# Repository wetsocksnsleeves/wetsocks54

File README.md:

# What
- 54 key ortholinear column staggered split keyboard
- Fork of cheapino, circuit utilises japanese matrix as well

# Future
- Working on v2 with better layout. Changing case and pcb
- Fixed some encoder issues in the pcb already

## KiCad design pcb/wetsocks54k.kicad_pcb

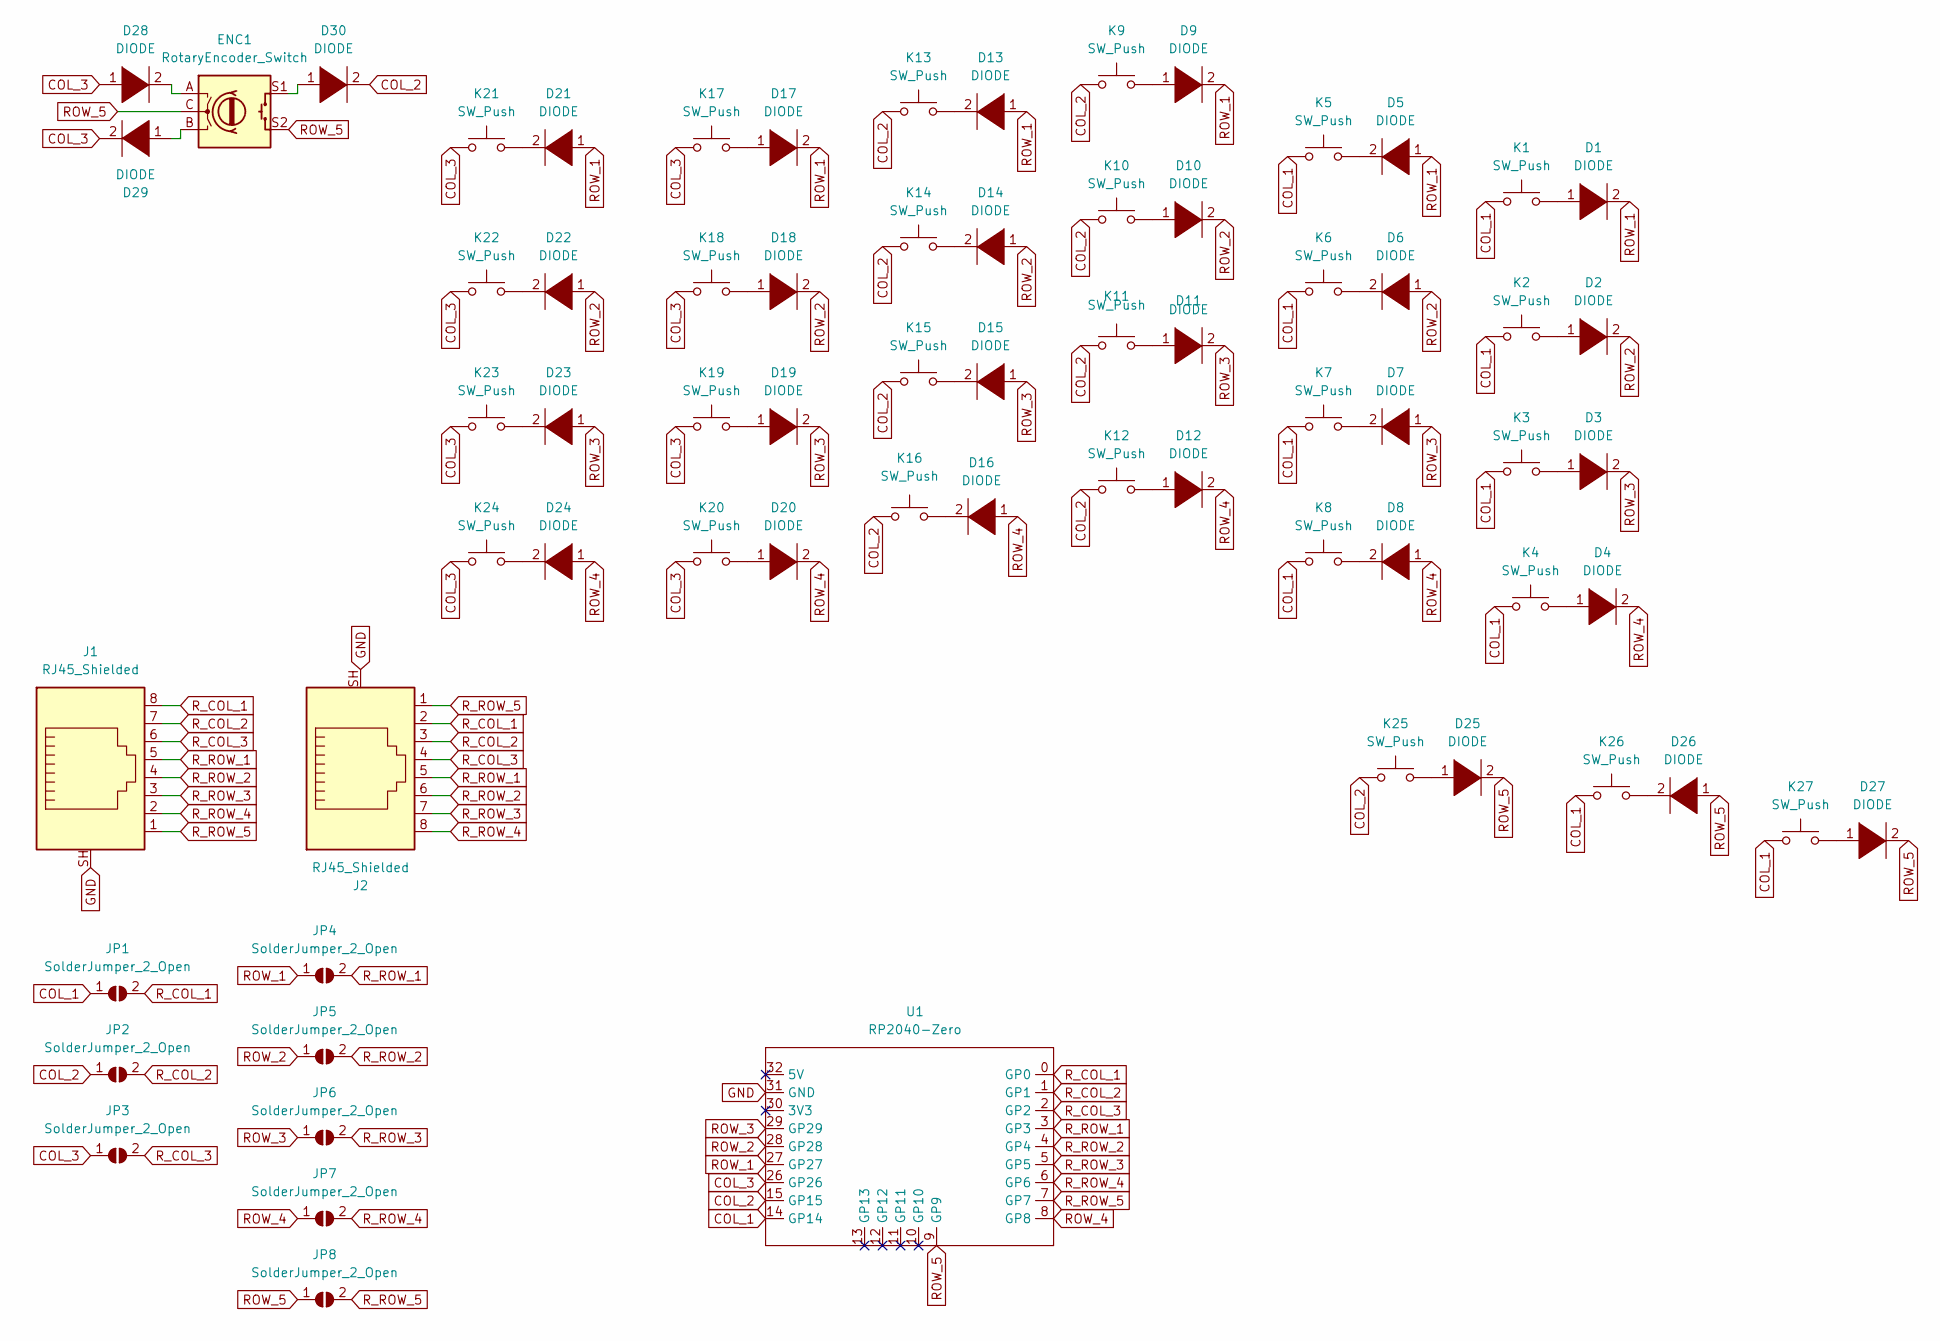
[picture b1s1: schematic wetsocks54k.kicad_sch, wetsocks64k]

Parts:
D1, D2, D3, D4, D5, D6, D7, D8, D9, D10, D11, D12, D13, D14, D15, D16, D17, D18, D19, D20, D21, D22, D23, D24, D25, D26, D27, D28, D29, D30: DIODE; Diode-dual
ENC1: RotaryEncoder_Switch; RotaryEncoder_Alps_EC11E-Switch_Vertical_H20mm
J1, J2: RJ45_Shielded; RJ45_Ninigi_GE
JP1, JP2, JP3, JP4, JP5, JP6, JP7, JP8: SolderJumper_2_Open; SolderJumper-2_P1.3mm_Open_TrianglePad1.0x1.5mm
K1, K2, K3, K4, K5, K6, K7, K8, K9, K10, K11, K12, K13, K14, K15, K16, K17, K18, K19, K20, K21, K22, K23, K24, K25, K26, K27: SW_Push; Kailh_socket_MX_optional_reversible
U1: RP2040-Zero; MCU_RP2040_Zero_34

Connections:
COL_1: JP1.1 (A), K1.1, K2.1, K3.1, K4.1, K5.1, K6.1, K7.1, K8.1, K26.1, K27.1, U1.14 (GP14)
COL_2: D30.2 (A), JP2.1 (A), K9.1, K10.1, K11.1, K12.1, K13.1, K14.1, K15.1, K16.1, K25.1, U1.15 (GP15)
COL_3: D28.1 (K), D29.2 (A), JP3.1 (A), K17.1, K18.1, K19.1, K20.1, K21.1, K22.1, K23.1, K24.1, U1.26 (GP26)
GND: J1.SH, J2.SH, U1.31 (GND)
unnamed: D1.1 (K), K1.2
unnamed: D2.1 (K), K2.2
unnamed: D3.1 (K), K3.2
unnamed: D4.1 (K), K4.2
unnamed: D5.2 (A), K5.2
unnamed: D6.2 (A), K6.2
unnamed: D7.2 (A), K7.2
unnamed: D8.2 (A), K8.2
unnamed: D9.1 (K), K9.2
unnamed: D10.1 (K), K10.2
unnamed: D11.1 (K), K11.2
unnamed: D12.1 (K), K12.2
unnamed: D13.2 (A), K13.2
unnamed: D14.2 (A), K14.2
unnamed: D15.2 (A), K15.2
unnamed: D16.2 (A), K16.2
unnamed: D17.1 (K), K17.2
unnamed: D18.1 (K), K18.2
unnamed: D19.1 (K), K19.2
unnamed: D20.1 (K), K20.2
unnamed: D21.2 (A), K21.2
unnamed: D22.2 (A), K22.2
unnamed: D23.2 (A), K23.2
unnamed: D24.2 (A), K24.2
unnamed: D25.1 (K), K25.2
unnamed: D26.2 (A), K26.2
unnamed: D27.1 (K), K27.2
unnamed: D28.2 (A), ENC1.A
unnamed: D29.1 (K), ENC1.B
unnamed: D30.1 (K), ENC1.S1
ROW_1: D1.2 (A), D5.1 (K), D9.2 (A), D13.1 (K), D17.2 (A), D21.1 (K), JP4.1 (A), U1.27 (GP27)
ROW_2: D2.2 (A), D6.1 (K), D10.2 (A), D14.1 (K), D18.2 (A), D22.1 (K), JP5.1 (A), U1.28 (GP28)
ROW_3: D3.2 (A), D7.1 (K), D11.2 (A), D15.1 (K), D19.2 (A), D23.1 (K), JP6.1 (A), U1.29 (GP29)
ROW_4: D4.2 (A), D8.1 (K), D12.2 (A), D16.1 (K), D20.2 (A), D24.1 (K), JP7.1 (A), U1.8 (GP8)
ROW_5: D25.2 (A), D26.1 (K), D27.2 (A), ENC1.C, ENC1.S2, JP8.1 (A), U1.9 (GP9)
R_COL_1: J1.8, J2.2, JP1.2 (B), U1.0 (GP0)
R_COL_2: J1.7, J2.3, JP2.2 (B), U1.1 (GP1)
R_COL_3: J1.6, J2.4, JP3.2 (B), U1.2 (GP2)
R_ROW_1: J1.5, J2.5, JP4.2 (B), U1.3 (GP3)
R_ROW_2: J1.4, J2.6, JP5.2 (B), U1.4 (GP4)
R_ROW_3: J1.3, J2.7, JP6.2 (B), U1.5 (GP5)
R_ROW_4: J1.2, J2.8, JP7.2 (B), U1.6 (GP6)
R_ROW_5: J1.1, J2.1, JP8.2 (B), U1.7 (GP7)

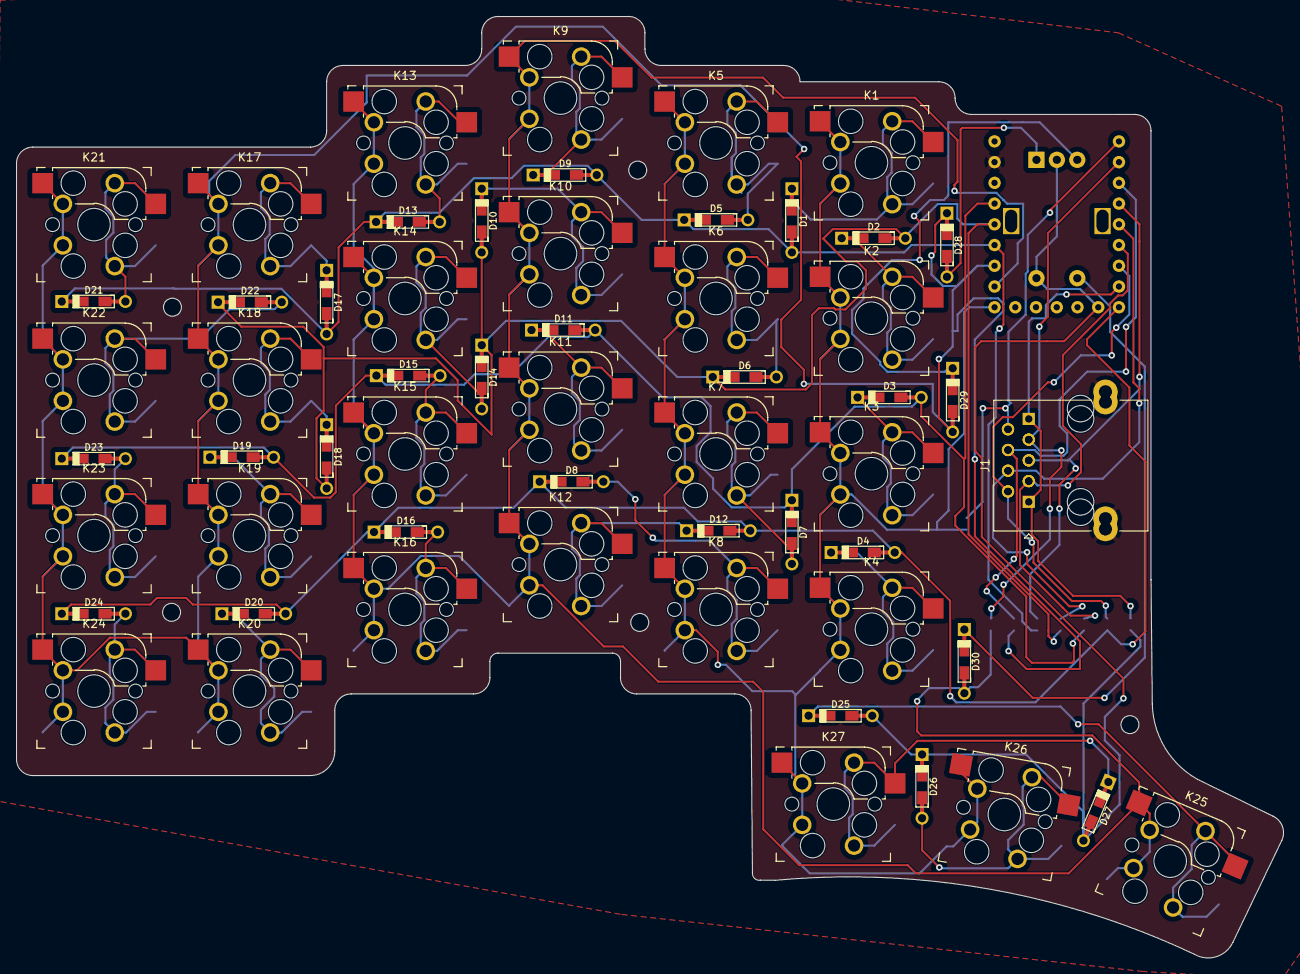
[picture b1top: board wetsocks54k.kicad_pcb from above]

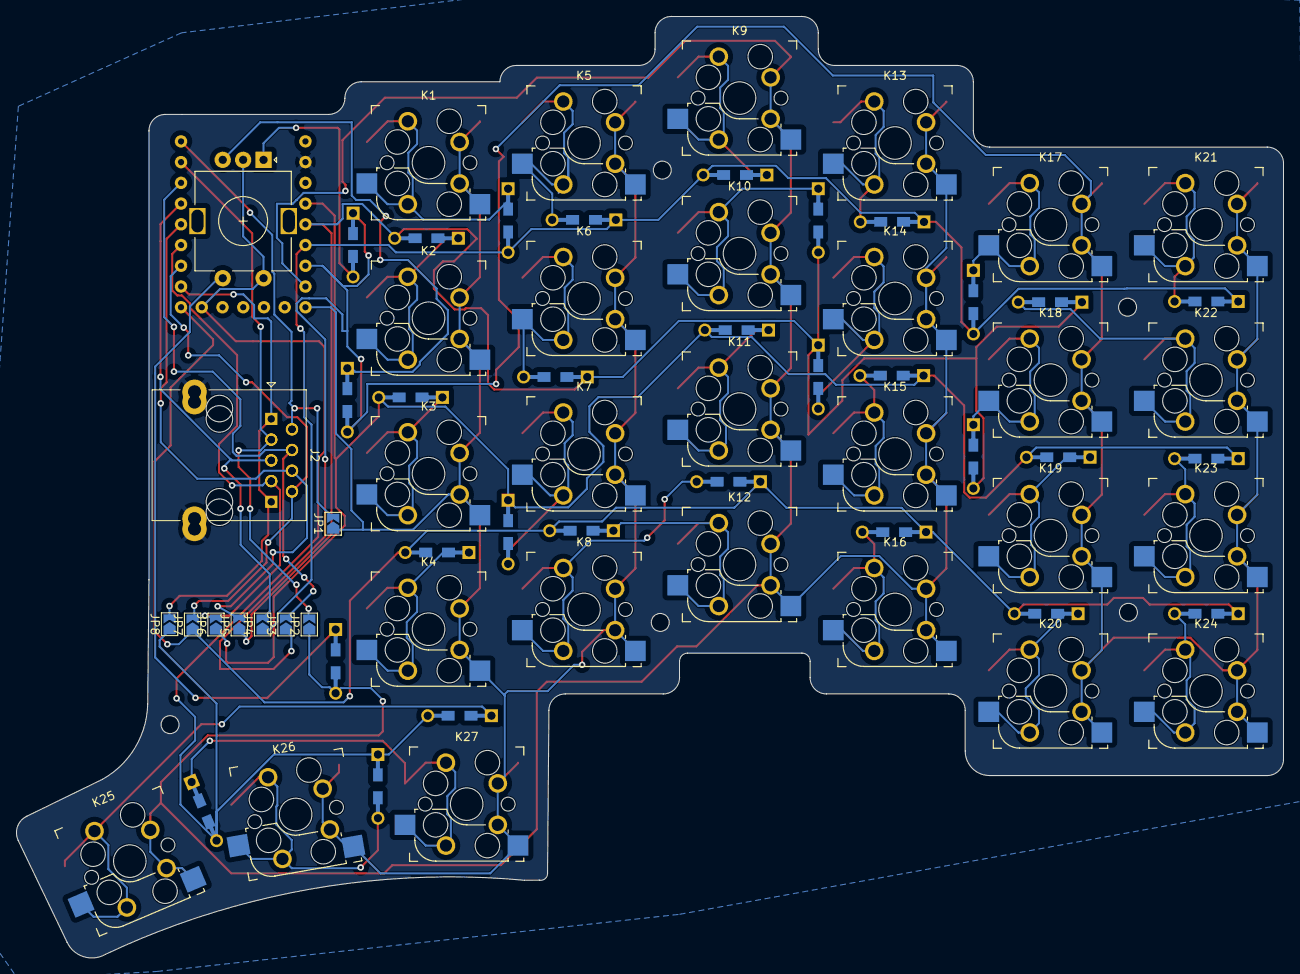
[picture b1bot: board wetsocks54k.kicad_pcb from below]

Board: 2 copper layers, 155.2 x 115.3 mm, 69 parts (10 on the bottom side), 47 nets.

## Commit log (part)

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2025-09-04 wetsocks54 v2.0 progress
